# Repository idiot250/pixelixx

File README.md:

# pixelixx

pixelixx is an audio/noise-reactive 16x16 rgb led dot matrix visualizer. it uses an esp32-s3 to process audio input and drive a 16x16 WS2812B RGB LED matrix, with 4 different visualization modes designed to represent the different aspect sounds as well as introduce uniqueness to the project. 

I've always been interested in music, and the first thing I thought of when thinking about a screen-centric project was whether i could create something like cava (the audio spectrum visualizer) using a pixelated screen (deliberately low-res). I built pixelixx to experiment with this idea, and also to create some cool peripherals for my desk. this project also gave me another oppurtunity (excuse) to learn more across several areas of engineering, such as circuit design, pcb layout, embedded programming, digital audio processing, and hardware integration. 

## features
 pixellix is designed around 4 visualization modes:
 - oscillator: animated wave patterns that respond to noise or audio
 - frequency spectrum: the most cava directly like one. frequency bars that represent different parts of the audio spectrum.
 - bubble: expanding/pulsating visual elements based on audio intensity.
 - colorfield: a continously changing field of color, with different frequency bands on different parts of the matrix.

 ## audio input
 pixelixx is designed around two audio sources:
 1. system audio: captures computer audio through a pipewire monitor and sends pcm data to the esp32-s3 over usb serial
 2. ambient noise: uses an inmp441 i2s microphone module to capture sound from the surrounding enviornment.

 the audio source can be selected independently of the visualization mode.

 ## components
 | component | purpose  |
 |---|---|
 |ESP32-S3-DevKitC-1-N16R8 | MCU |
 |16x16 WS2812B RGB LED Matrix | Visual output | 
 |INMP441 Mic module | audio input|
 |74AHCT125 | LED data level shifting |
 |KY-040 EC11 Rotary encoder  | Physical interface|
 |Push button | mode selection|
 |external 5v supply| led matrix power |

 ## firmware and software
 the firmware was developed using esp-idf.
 
 software responsibilities include: 
 - acquiring audio samples from source
 - calculating audio intensity and frequency
 - mapping audio data to visualization patterns
 - generating led patterns
 - handling user input and mode selection

 ## project status
 
 ### ver 1: initial hardware prototype/PoC
 the initial design focuses on proving the firmware is functional, and that the hardware all works as intended: the esp32-s3 interface, audio input, led data circuitry, power distribution, and user controls.

 firmware development and hardware testing will bring the visualization modes together into a working device. 

 ## future improvements
 - refine audio processing
 - improve frequency analysis
 - add more visualization modes
 - develop an enclosure
 - explore audio playback capabilities (ie. showing the visualizer while playing the audio)
 - wirelessly recieving audio input data from pipewire

 ## resources and acknowledgement
 built as an independent electronics and embedded systems project using kicad and esp-idf.

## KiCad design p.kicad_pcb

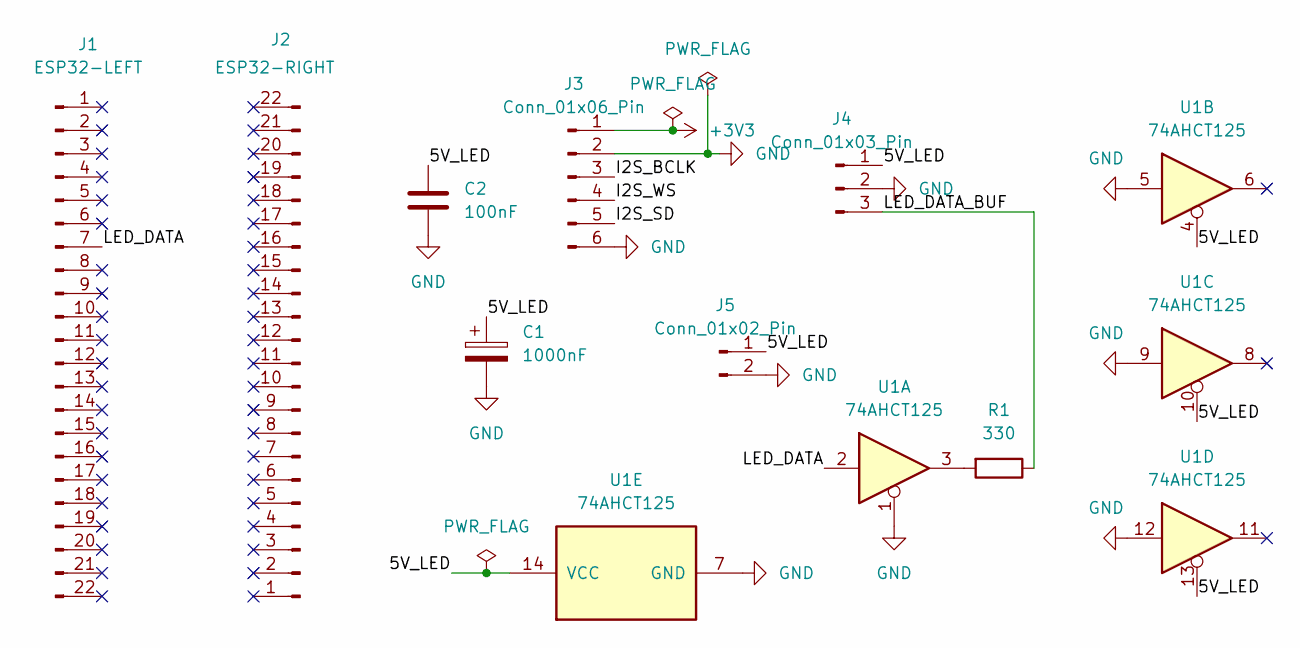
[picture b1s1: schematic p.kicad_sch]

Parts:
C1: 1000nF; CP_Radial_D10.0mm_P5.00mm
C2: 100nF; C_0805_2012Metric
J1: ESP32-LEFT; PinSocket_1x22_P2.54mm_Vertical
J2: ESP32-RIGHT; PinSocket_1x22_P2.54mm_Vertical
J3: Conn_01x06_Pin; PinSocket_1x06_P2.54mm_Vertical
J4: Conn_01x03_Pin; PinSocket_1x03_P2.54mm_Vertical
J5: Conn_01x02_Pin; TerminalBlock_Phoenix_MKDS-1,5-2_1x02_P5.00mm_Horizontal
R1: 330; R_0805_2012Metric
U1: 74AHCT125; SOIC-14_3.9x8.7mm_P1.27mm

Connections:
+3V3: J3.1
/5V_LED: C1.1, C2.1, J4.1, J5.1, U1.4, U1.10, U1.13, U1.14 (VCC)
/I2S_BCLK: J3.3
/I2S_SD: J3.5
/I2S_WS: J3.4
/LED_DATA: J1.7 (Pin_7_7), U1.2
/LED_DATA_BUF: J4.3, R1.1
GND: C1.2, C2.2, J3.2, J3.6, J4.2, J5.2, U1.1, U1.5, U1.7 (GND), U1.9, U1.12
unnamed: R1.2, U1.3

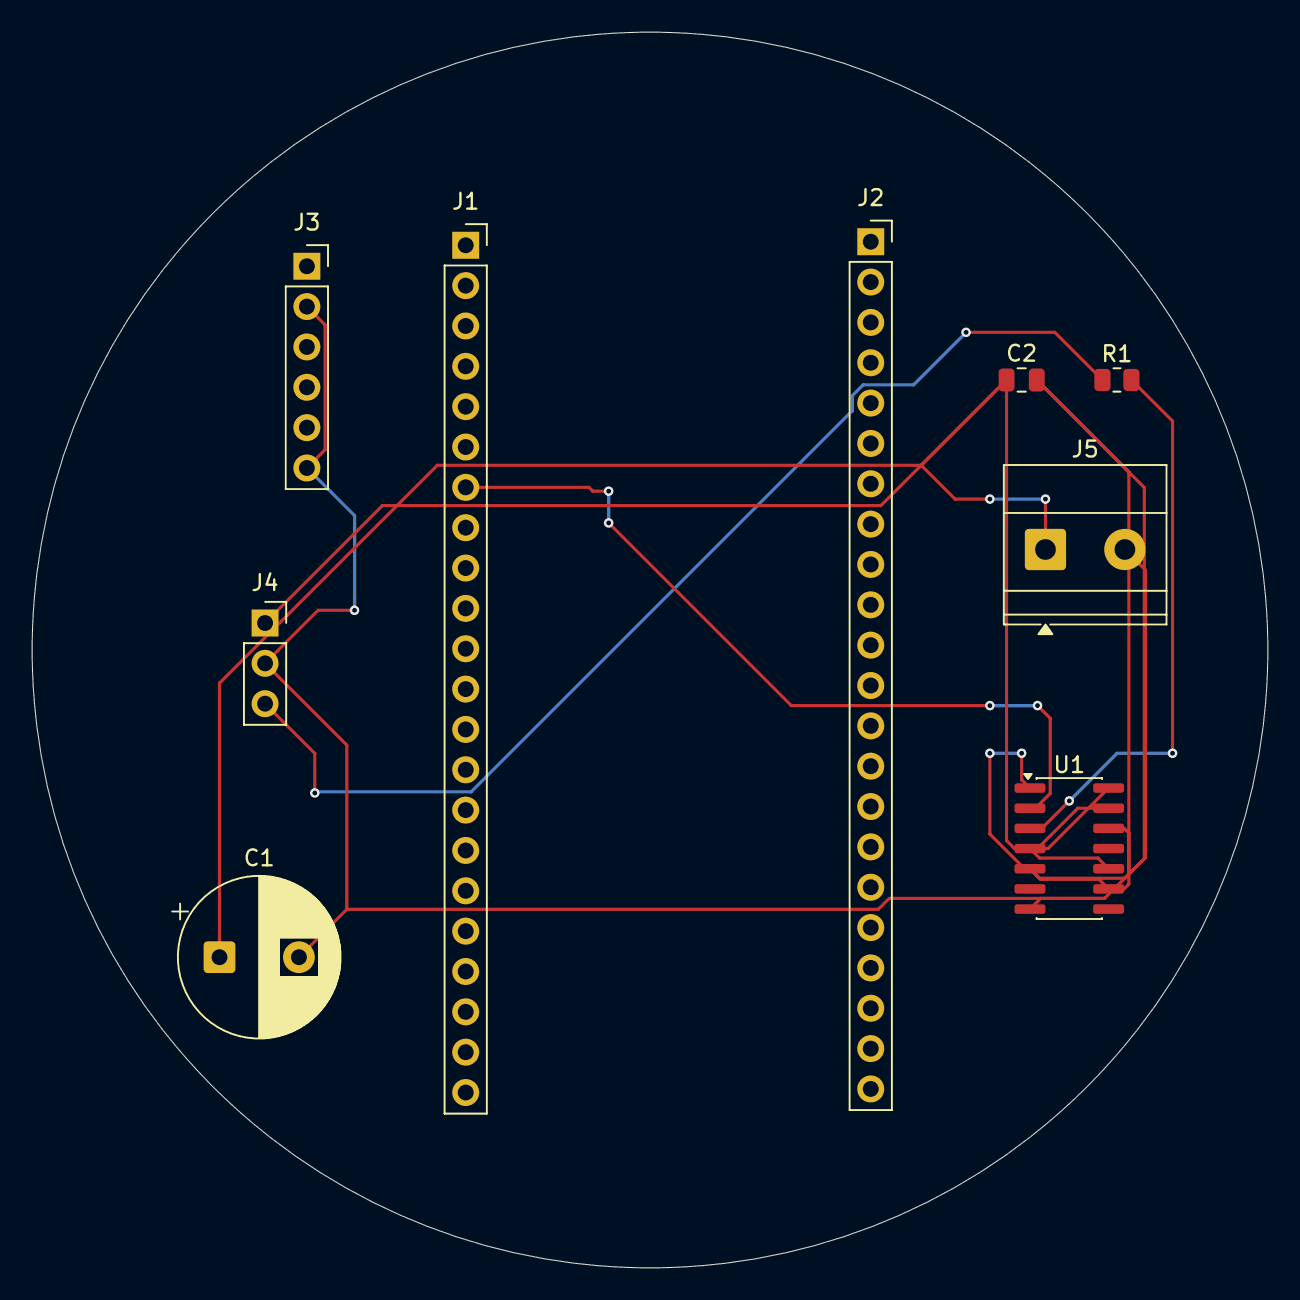
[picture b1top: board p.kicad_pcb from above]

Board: 2 copper layers, 77.8 x 77.8 mm, 9 parts (0 on the bottom side), 5 nets.
